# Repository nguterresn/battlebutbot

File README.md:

# BattleButBot: Your Ultimate Antweight Pusher Robot Companion

BattleButBot is a small (<10x8cm) and light (<150g) robot designed specifically for the [Antweight class of robot combat events](https://www.robotwars101.org/ants/rules.htm). With its sleek design, sturdy construction, and advanced control features, BattleButBot is the perfect choice for robot fighting enthusiasts of all skill levels.

## Features

* **Intuitive Web-based Control**: BattleButBot can be easily controlled from any device with a [web browser](#web-robot-controller), allowing you to take full control of your robot in real-time.
* **Powerful Motors**: BattleButBot's brush DC motors provide great performance and speed, allowing your robot to deliver powerful moves.
* **Durable Build**: BattleButBot is built to withstand the toughest battles in Antweight robot combat events. Its rugged construction and impact-resistant design ensure that your robot stays in one piece, no matter how intense the fight gets.
* **Easy to Use**: BattleButBot is easy to use and requires no special skills or training. With its intuitive controls and simple setup process, you can start battling right away.

🎉 **NEW**: The BattleButBot supports [ESPNow](https://www.espressif.com/en/solutions/low-power-solutions/esp-now) protocol, thus provinding another way to be externally controlled. Check the [simple esp-now controller](https://github.com/nguterresn/simple-esp-now-controller) to know more.

## Requirements

**Cheap**: Priced under $50

* ✅ Costs 50$.

**Weight**: Equal or less than 150 milligrams

* ✅ Weigths ~110g. (PLA printed)

**Acessable**: All parts are easily available (can be obtained from anywhere)

* ✅ Parts can be found on [LCSC](lcsc.com), [Digikey](digikey.com) or [AliExpress](https://www.aliexpress.us).

**Flexible**: Can be controlled over WiFi

* ✅ Easy to use web browser GUI

**Simple**: All hardware components are easy to assemble

* ✅ The device uses [PH sockets](https://www.jst-mfg.com/product/index.php?series=199) and requires a few screws.

**Portable**: Powered by a battery

* ✅ Small and light weight 2S 7.4V battery (58 x 18 x 19 mm).

## ESPNow Controller

Take a look [here](https://github.com/nguterresn/simple-esp-now-controller).

## Web Robot Controller

Connect to the `BattleButBot` network using WiFi.

Open `bot.local` on you browser.

To control the BattleButBot, simply use both **joysticks** located in the screen.

> [!NOTE]
> Before submitting a issue ticket, please use another browser as Safari is not 100% stable for a web browser controller.

### Robot Controls

You can control BattleButBot using the joysticks from the graphical user interface (GUI). To move forward, drag the left joystick upwards, and to move backward, drag the left joystick downwards. To lean the BattleButBot to the right, drag the right joystick to the right and vice-versa.

### Settings

To configure your joystick settings, click the `Settings` button.

For ease of development while the robot firmware is in development, a console log is located at the bottom of the screen.

## How to order

### Shopping list:

| Hardware                                                                                                                                                                                                                                                                                                                                                                                                                                                        | Qty | Price                           |
| --------------------------------------------------------------------------------------------------------------------------------------------------------------------------------------------------------------------------------------------------------------------------------------------------------------------------------------------------------------------------------------------------------------------------------------------------------------- | --- | ------------------------------- |
| [N20 Gear Motor 6V 600RPM](https://www.aliexpress.us/item/3256803245120861.html?spm=a2g0o.productlist.main.3.be16dmKLdmKLdh&algo_pvid=1b8b9a20-a58e-4537-a37a-af46f9d1652b&algo_exp_id=1b8b9a20-a58e-4537-a37a-af46f9d1652b-1&pdp_npi=4%40dis%21SEK%2125.63%2119.17%21%21%212.34%211.75%21%40211b61a417119945526086789eb5a6%2112000025761667070%21sea%21SE%210%21AB&curPageLogUid=N7UsGzjkJw8d&utparam-url=scene%3Asearch%7Cquery_from%3A&gatewayAdapt=glo2usa) | 2   | 1.36$ x 2 + 2.27$ shipping      |
| [Wheels](https://www.aliexpress.com/item/33026783171.html?spm=a2g0o.order_list.order_list_main.102.76381802470tYv)                                                                                                                                                                                                                                                                                                                                              | 2   | ~1$ + 4$ shipping               |
| [BOM](https://github.com/nguterresn/battlebutbot/blob/main/board/bubblebutbot/production/bom.csv)                                                                                                                                                                                                                                                                                                                                     | 1   | ~10$ + 10$ [shipping](LCSC.com) |
| [PCB](https://github.com/nguterresn/battlebutbot/blob/main/board/bubblebutbot/production/bubblebutbot.zip)                                                                                                                                                                                                                                                                                                                                  | 5   | ~2$ + 3$ [shipping](jlcpcb.com) |
| [2S LiPo](https://botland.store/battery-li-pol-2s-74-v/570-li-poly-dualsky-520mah-25c-2s-74v-6941047107427.html)                                                                                                                                                                                                                                                                                                                                                | 1   | 8$                              |
| Total                                                                                                                                                                                                                                                                                                                                                                                                                                                           | -   | ~50$                            |

When ordering the BOM, make sure to order at least 5 (five!) of each component so you end up with the possibility to solder 5 different PCBs.

### Supply chain troubleshooting

⚠️ In case a few componenets are not available refer to the list below:

- Any ESP32-S3-WROOM-1 (NOT 1U!) should work. There are a [few variations](https://www.lcsc.com/search?q=ESP32-S3-WROOM-1) of the same footprint with more or less RAM and FLASH.
- H1-H4 componenets are mount holes, they don't need any component assigned.
- In case of resistor or capacitors shortage, it is also OK to find other supplier as long as it follows the same specification (e.g. 20k resistor 5%)

## Design

The design of the BattleButBot plays an important role. How it is designed determines how heavy (or how light) it is. Two requirements: sturdy and light.

### Cyberpunk

A cyberpunk alike robot is cold as hell. The low poly edges also make it easier to print.

## Assemble

What you need:

* 6 M3 8mm/5mm screws
* 6 Heat inserts
* The [body](https://github.com/nguterresn/battlebutbot/blob/main/body/Car.stl)
* The [lid](https://github.com/nguterresn/battlebutbot/blob/main/body/Lid.stl)
* The [front](https://github.com/nguterresn/battlebutbot/blob/main/body/Gate.stl)
* A 2S-7.4V Battery
* The [PCB](https://github.com/nguterresn/battlebutbot/tree/main/board/bubblebutbot)
* The two wheels

### Battery

Place the battery close to the front of the bot.

Place the switch.

### Motors

Place both motors with the gears facing the top (to prevent any friction with the bottom).

### PCB

Before screwing the PCB down, finish all the connections.

Place the PCB and the lid, and screw it down.

## Develop

Clone the project by running the following command:

```bash
git clone git@github.com:nguterresn/battlebutbot.git
```

### Tools

* VSCode with PlatformIO
* Fusion360

### 3rd Party Libraries

* [ESPAsyncWebServer](https://github.com/me-no-dev/ESPAsyncWebServer)
* [Joystick 2](https://github.com/bobboteck/JoyStick)

## Support

If you have any questions or issues with the BattleButBot, please contact guterresnogueira@gmail.com.

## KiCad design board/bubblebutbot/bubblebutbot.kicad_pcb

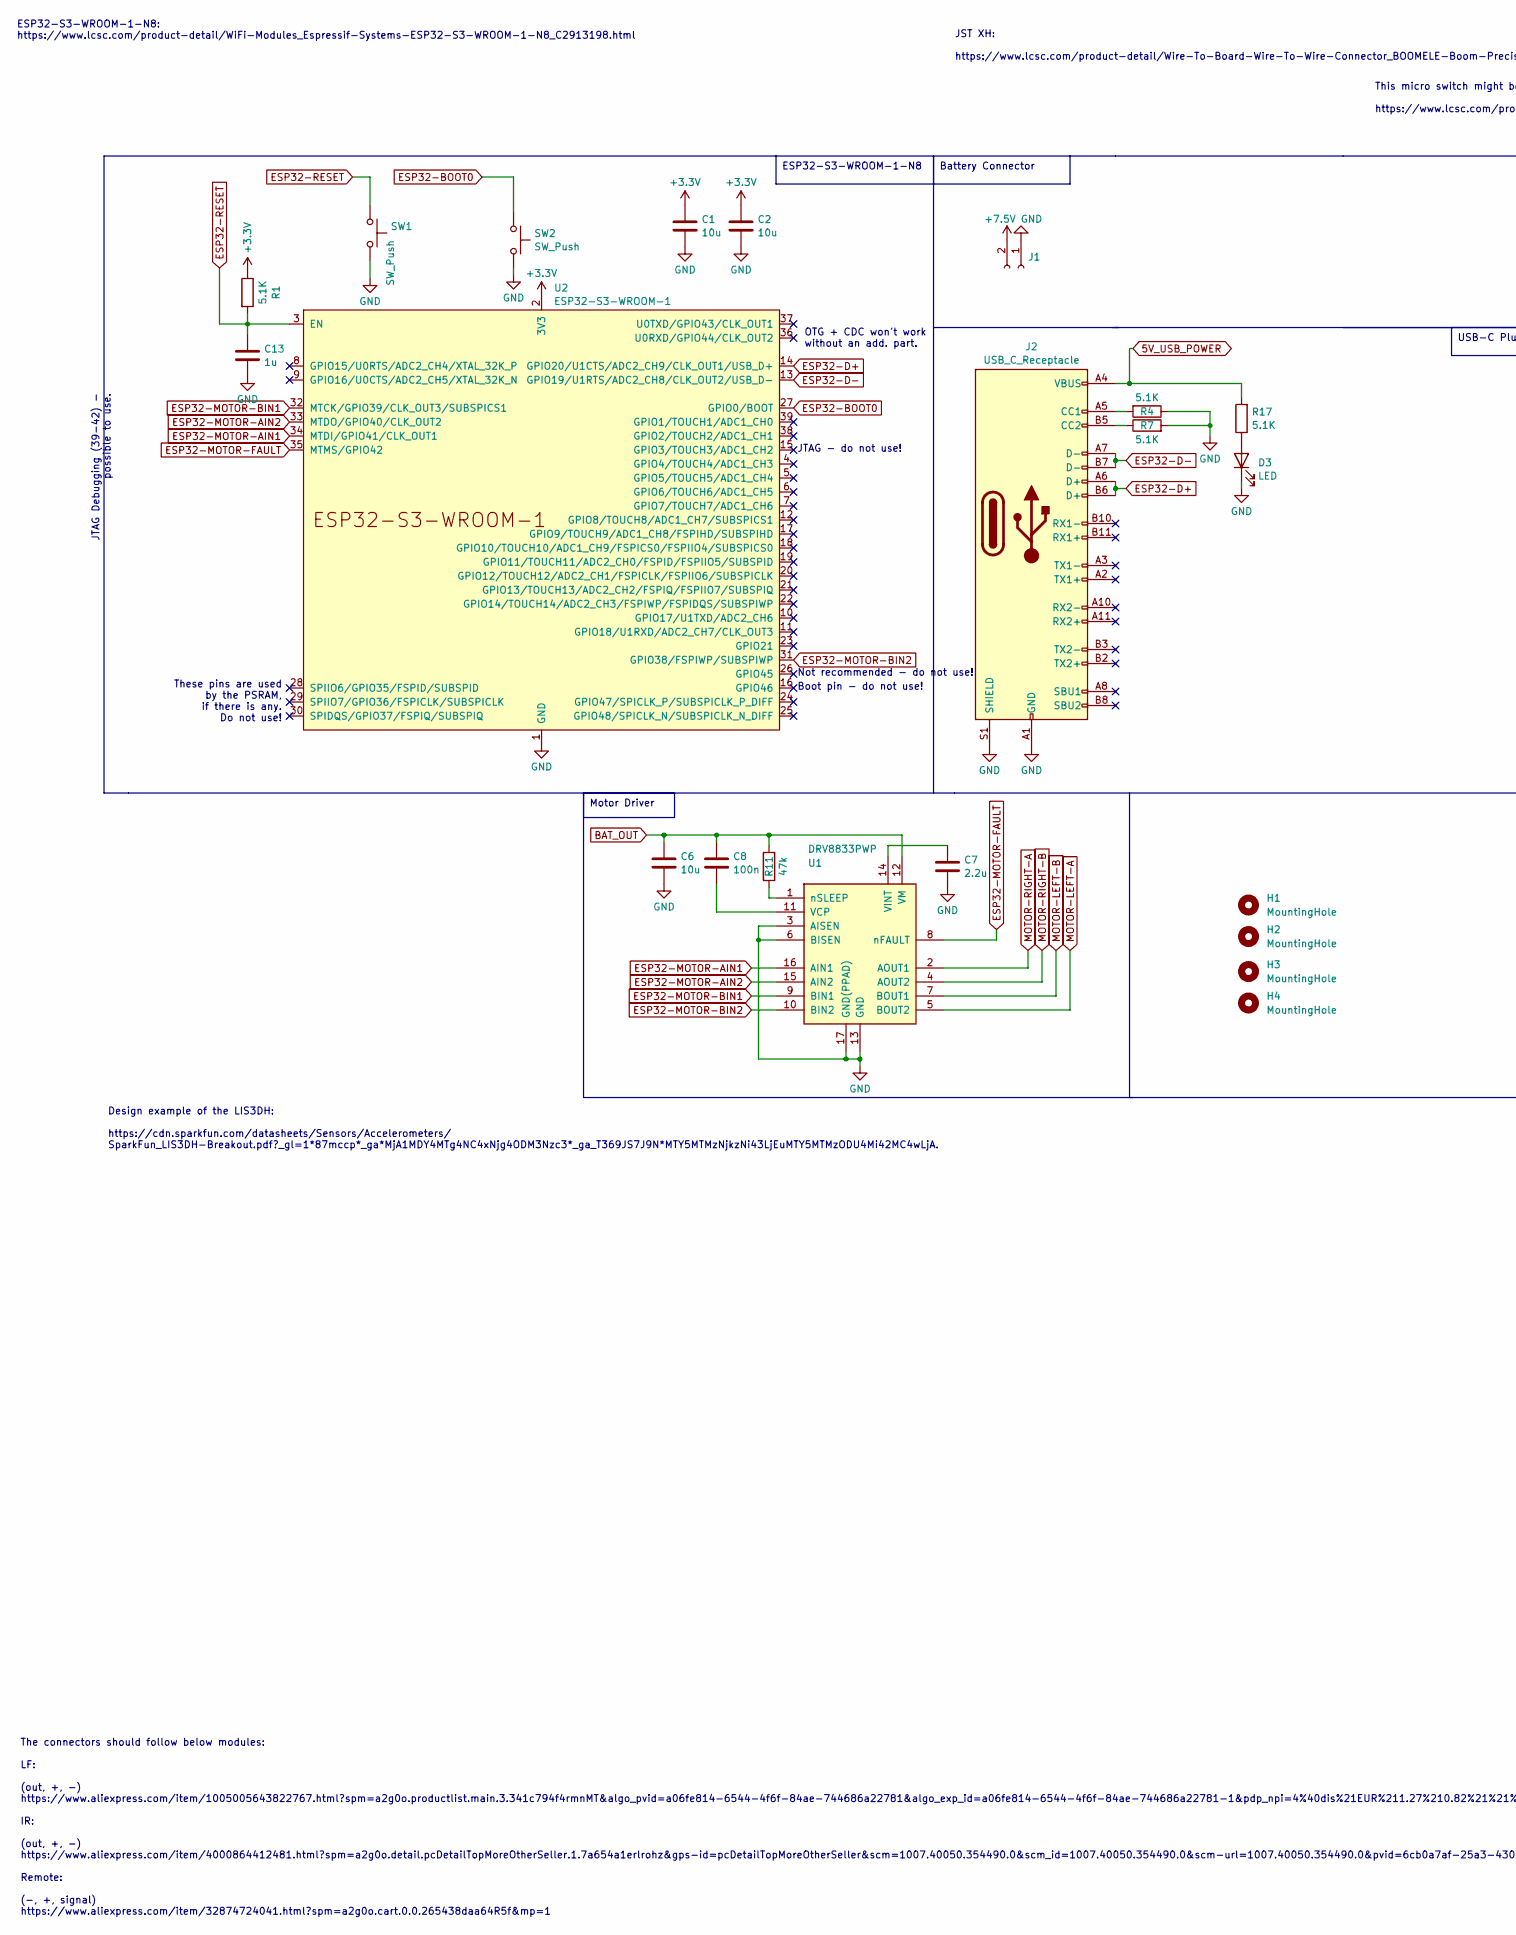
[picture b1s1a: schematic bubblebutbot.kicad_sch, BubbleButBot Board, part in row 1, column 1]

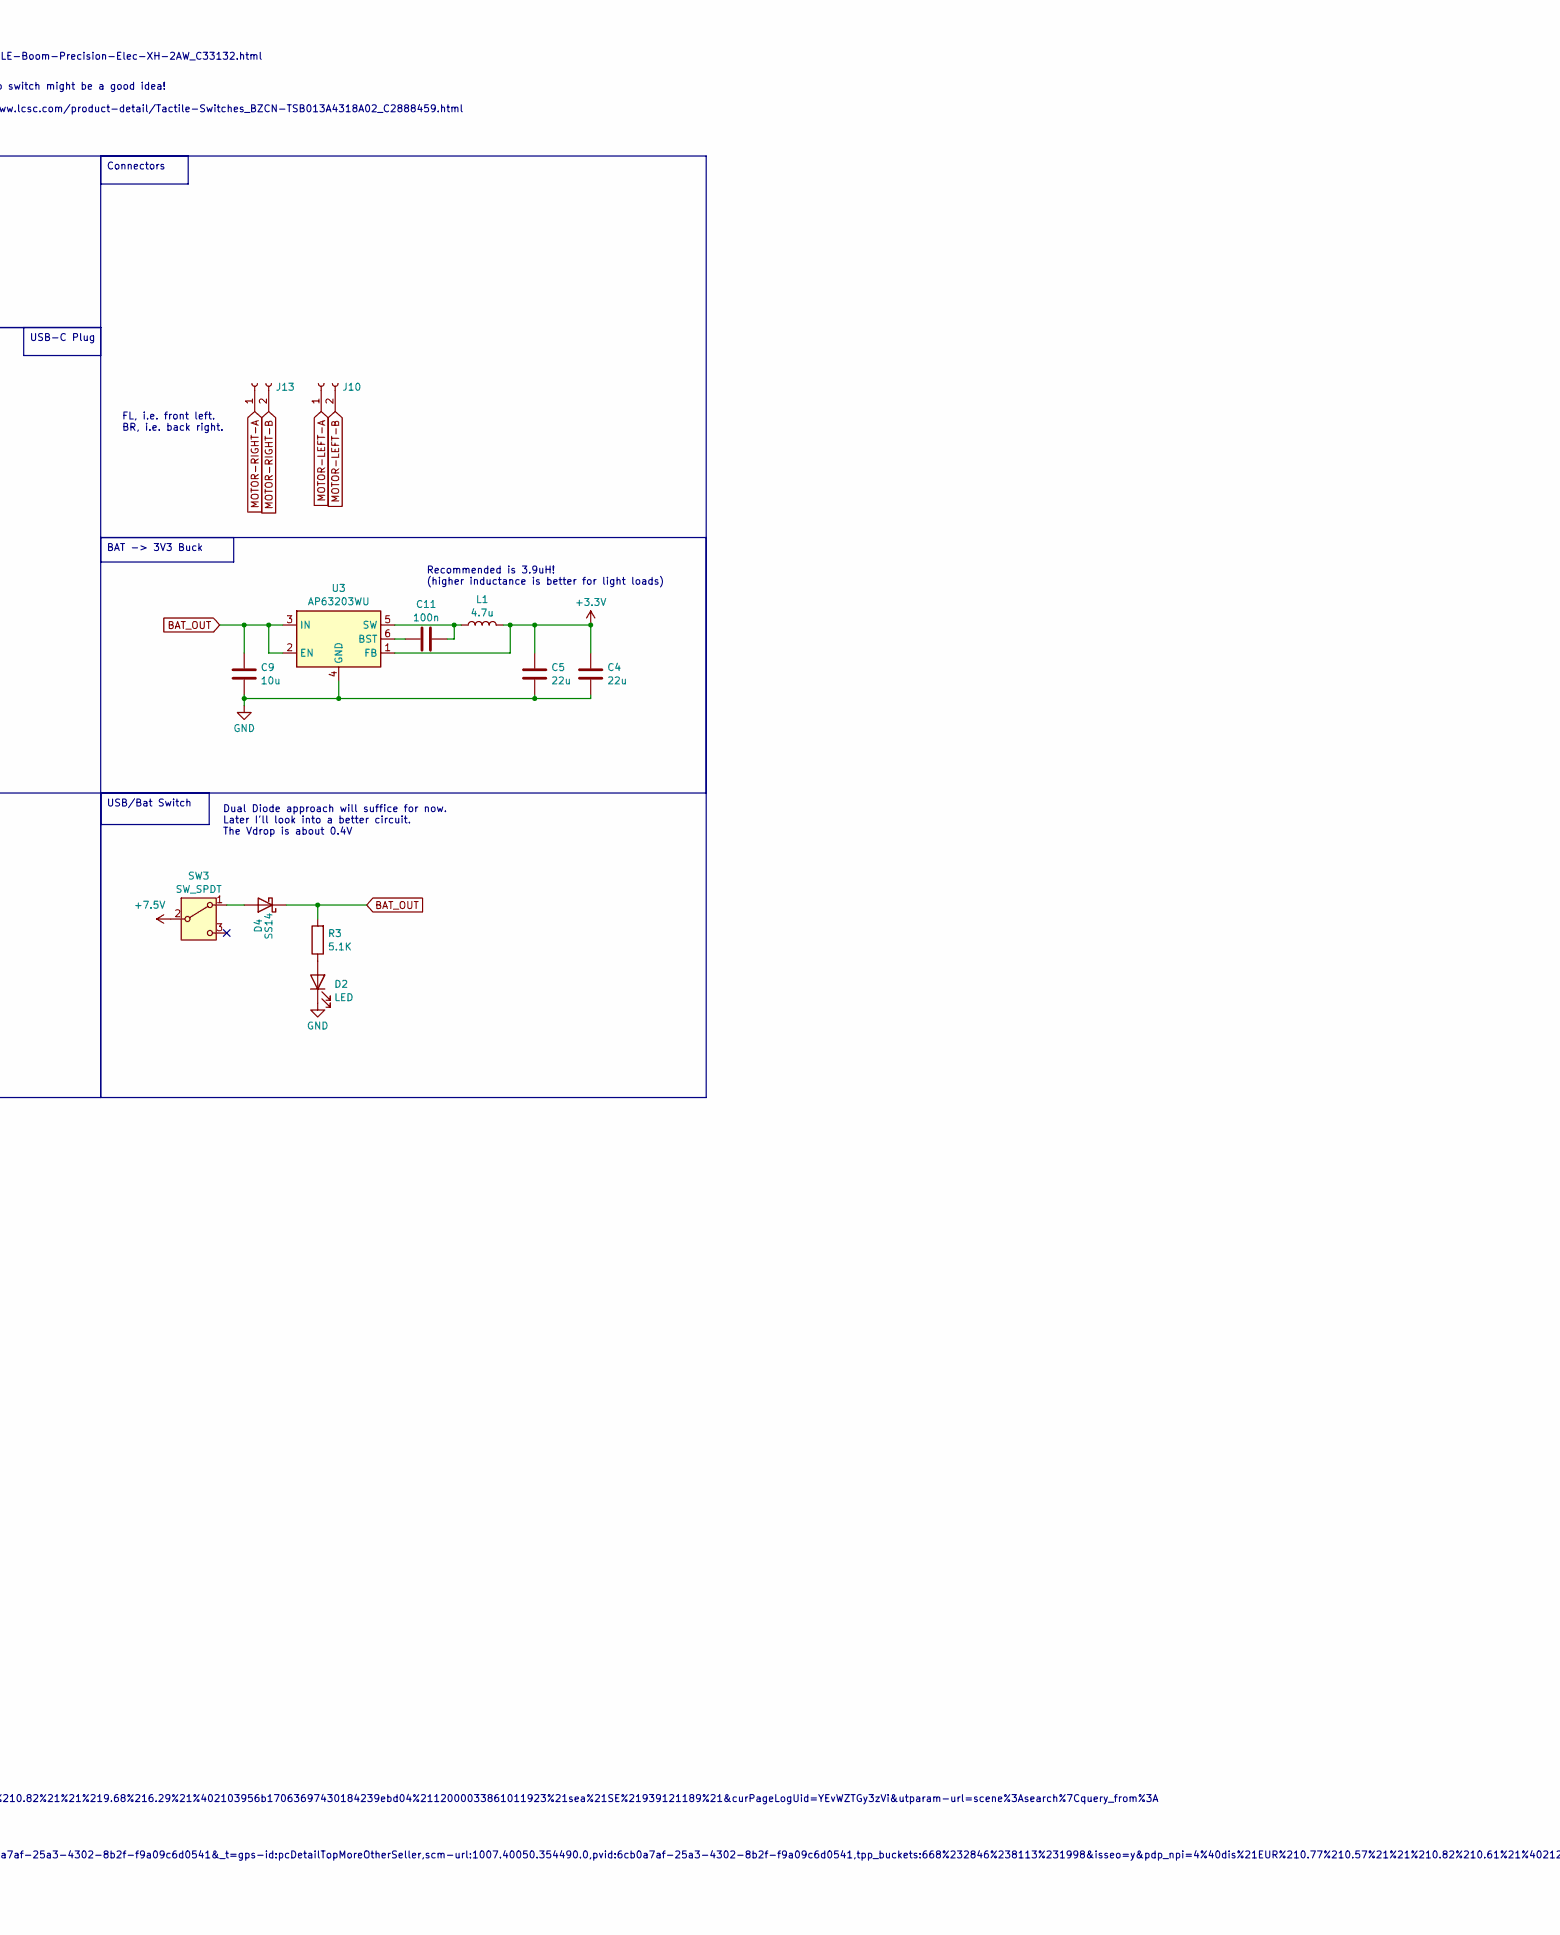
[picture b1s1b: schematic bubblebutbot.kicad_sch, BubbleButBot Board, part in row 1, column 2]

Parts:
C1, C2, C9: 10u; C_0603_1608Metric_Pad1.08x0.95mm_HandSolder; LCSC C380316
C4, C5: 22u; C_1206_3216Metric_Pad1.33x1.80mm_HandSolder; LCSC C12891
C6: 10u; C_1206_3216Metric_Pad1.33x1.80mm_HandSolder; LCSC C47971
C7: 2.2u; C_0603_1608Metric_Pad1.08x0.95mm_HandSolder; LCSC C2691406
C8, C11: 100n; C_0603_1608Metric_Pad1.08x0.95mm_HandSolder; LCSC C282519
C13: 1u; C_0603_1608Metric_Pad1.08x0.95mm_HandSolder; LCSC C1592
D2, D3: LED; LED_0603_1608Metric_Pad1.05x0.95mm_HandSolder; LCSC C965799
D4: SS14; D_SMA; LCSC C2480
H1, H2, H3, H4: MountingHole; MountingHole_3.2mm_M3_ISO14580_Pad
J1, J10, J13: JST XH; JST_PH_S2B-PH-K_1x02_P2.00mm_Horizontal; LCSC C722769
J2: USB_C_Receptacle; USB_C_Receptacle_GCT_USB4105-xx-A_16P_TopMnt_Horizontal; LCSC C2765186
L1: 4.7u; L_Wuerth_WE-TPC-3816; LCSC C2879693
R1, R3, R4, R7, R17: 5.1K; R_0603_1608Metric_Pad0.98x0.95mm_HandSolder; LCSC C2907114
R11: 47k; R_0603_1608Metric_Pad0.98x0.95mm_HandSolder; LCSC C2907173
SW1, SW2: SW_Push; SW_SPST_CK_RS282G05A3; LCSC C2888455
SW3: SW_SPDT; SW_Slide_SPDT_Straight_CK_OS102011MS2Q; LCSC C2939725
U1: DRV8833PWP; HTSSOP-16-1EP_4.4x5mm_P0.65mm_EP3.4x5mm_Mask2.46x2.31mm_The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; LCSC C50506
U2: ESP32-S3-WROOM-1; LCSC C2913198
U3: AP63203WU; TSOT-23-6; LCSC C780769

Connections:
5V_USB_POWER: J2.A4 (VBUS), J2.A9 (VBUS), J2.B4 (VBUS), J2.B9 (VBUS), R17.2
+3.3V: C1.1, C2.1, C4.1, C5.1, L1.2, R1.1, U2.2 (3V3), U3.1 (FB)
+7.5V: J1.2, SW3.2 (B)
BAT_OUT: C6.1, C8.2, C9.1, D4.1 (K), R3.2, R11.2, U1.12 (VM), U3.2 (EN), U3.3 (IN)
ESP32-BOOT0: SW2.1, U2.27 (GPIO0/BOOT)
ESP32-D+: J2.A6 (D+), J2.B6 (D+), U2.14 (GPIO20/U1CTS/ADC2_CH9/CLK_OUT1/USB_D+)
ESP32-D-: J2.A7 (D-), J2.B7 (D-), U2.13 (GPIO19/U1RTS/ADC2_CH8/CLK_OUT2/USB_D-)
ESP32-MOTOR-AIN1: U1.16 (AIN1), U2.34 (MTDI/GPIO41/CLK_OUT1)
ESP32-MOTOR-AIN2: U1.15 (AIN2), U2.33 (MTDO/GPIO40/CLK_OUT2)
ESP32-MOTOR-BIN1: U1.9 (BIN1), U2.32 (MTCK/GPIO39/CLK_OUT3/SUBSPICS1)
ESP32-MOTOR-BIN2: U1.10 (BIN2), U2.31 (GPIO38/FSPIWP/SUBSPIWP)
ESP32-MOTOR-FAULT: U1.8 (nFAULT), U2.35 (MTMS/GPIO42)
ESP32-RESET: C13.1, R1.2, SW1.1, U2.3 (EN)
GND: C1.2, C2.2, C4.2, C5.2, C6.2, C7.2, C9.2, C13.2, D2.1 (K), D3.1 (K), J1.1, J2.A1 (GND), J2.A12 (GND), J2.B1 (GND), J2.B12 (GND), J2.S1 (SHIELD), R4.1, R7.2, SW1.2, SW2.2, U1.3 (AISEN), U1.6 (BISEN), U1.13 (GND), U1.17 (GND(PPAD)), U2.1 (GND), U2.40 (GND), U2.41 (GND), U3.4 (GND)
MOTOR-LEFT-A: J10.1, U1.5 (BOUT2)
MOTOR-LEFT-B: J10.2, U1.7 (BOUT1)
MOTOR-RIGHT-A: J13.1, U1.2 (AOUT1)
MOTOR-RIGHT-B: J13.2, U1.4 (AOUT2)
unnamed: D2.2 (A), R3.1
unnamed: D3.2 (A), R17.1
unnamed: D4.2 (A), SW3.1 (A)
unnamed: J2.A5 (CC1), R4.2
unnamed: J2.B5 (CC2), R7.1
unnamed: C8.1, U1.11 (VCP)
unnamed: C7.1, U1.14 (VINT)
unnamed: R11.1, U1.1 (nSLEEP)
unnamed: C11.2, U3.6 (BST)
unnamed: C11.1, L1.1, U3.5 (SW)

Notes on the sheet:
Battery Connector
USB-C Plug
BAT -> 3V3 Buck
USB/Bat Switch
Connectors
Motor Driver
ESP32-S3-WROOM-1-N8
ESP32-S3-WROOM-1-N8: https://www.lcsc.com/product-detail/WiFi-Modules_Espressif-Systems-ESP32-S3-WROOM-1-N8_C2913198.html
This micro switch might be a good idea! https://www.lcsc.com/product-detail/Tactile-Switches_BZCN-TSB013A4318A02_C2888459.html
Design example of the LIS3DH: https://cdn.sparkfun.com/datasheets/Sensors/Accelerometers/ SparkFun_LIS3DH-Breakout.pdf?_gl=1*87mccp*_ga*MjA1MDY4MTg4NC4xNjg4ODM3Nzc3*_ga_T369JS7J9N*MTY5MTMzNjkzNi43LjEuMTY5MTMzODU4Mi42MC4wLjA.
JTAG Debugging (39-42) - possible to use.
JST XH: https://www.lcsc.com/product-detail/Wire-To-Board-Wire-To-Wire-Connector_BOOMELE-Boom-Precision-Elec-XH-2AW_C33132.html
JTAG - do not use!
Dual Diode approach will suffice for now. Later I'll look into a better circuit. The Vdrop is about 0.4V
OTG + CDC won't work without an add. part.
The connectors should follow below modules: LF: (out, +, -) https://www.aliexpress.com/item/1005005643822767.html?spm=a2g0o.productlist.main.3.341c794f4rmnMT&algo_pvid=a06fe814-6544-4f6f-84ae-744686a22781&algo_exp_id=a06fe814-6544-4f6f-84ae-744686a22781-1&pdp_npi=4%40dis%21EUR%211.27%210.82%21%21%2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
Boot pin - do not use!
FL, i.e. front left. BR, i.e. back right.
These pins are used by the PSRAM, if there is any. Do not use!
Recommended is 3.9uH! (higher inductance is better for light loads)
Not recommended - do not use!

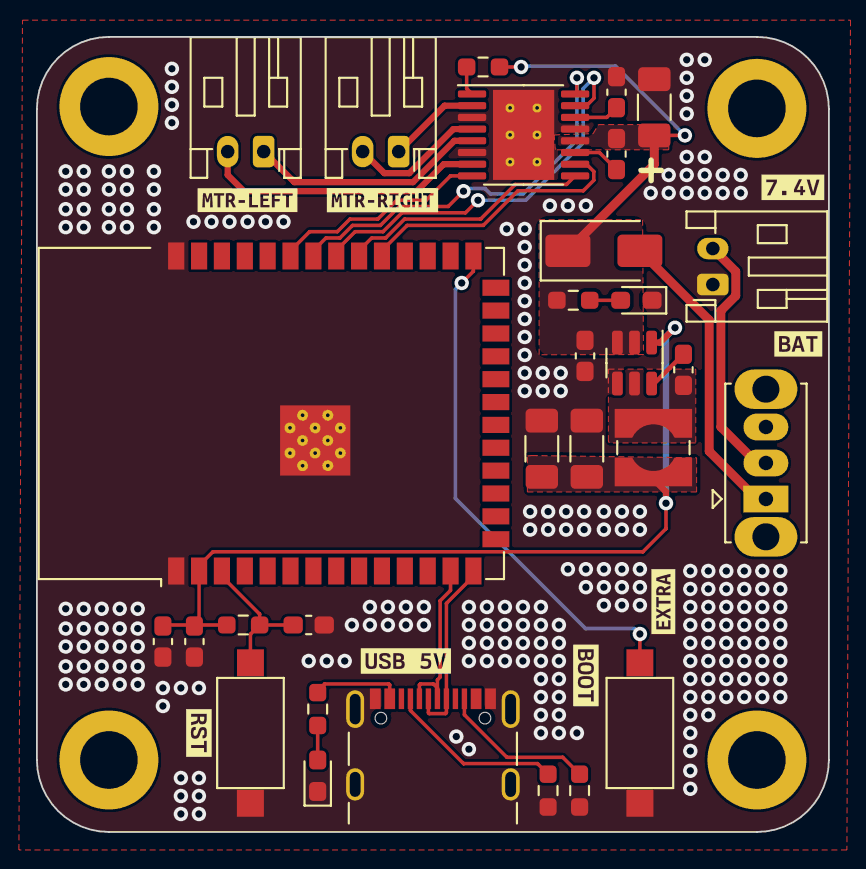
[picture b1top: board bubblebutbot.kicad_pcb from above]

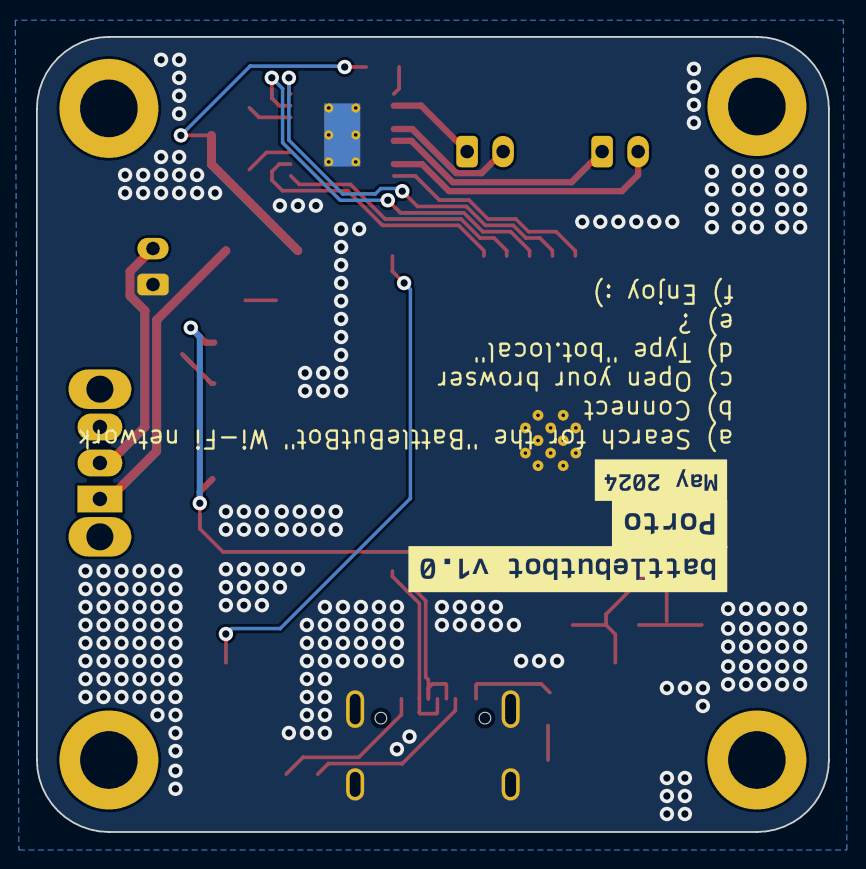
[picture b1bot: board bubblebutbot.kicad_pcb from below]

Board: 2 copper layers, 44.0 x 44.2 mm, 45 parts (3 on the bottom side), 28 nets.

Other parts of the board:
kibuzzard-65B53DEB: G***; kibuzzard-65B53DEB
kibuzzard-65B534AD: G***; kibuzzard-65B534AD
kibuzzard-65B534B8: G***; kibuzzard-65B534B8
kibuzzard-65B5357F: G***; kibuzzard-65B5357F
kibuzzard-65B52192: G***; kibuzzard-65B52192
kibuzzard-65B53096: G***; kibuzzard-65B53096
kibuzzard-65B53575: G***; kibuzzard-65B53575
kibuzzard-661BA04B: G***; kibuzzard-661BA04B
kibuzzard-664E35A6: G***; kibuzzard-664E35A6
kibuzzard-664E35B1: G***; kibuzzard-664E35B1
kibuzzard-664E35C5: G***; kibuzzard-664E35C5

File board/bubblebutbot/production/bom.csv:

Designator,Footprint,Quantity,Value,LCSC Part #
"C1, C2, C9",0603,3,10u,C380316
"C11, C8",0603,2,100n,C282519
C13,0603,1,1u,C1592
"C4, C5",1206,2,22u,C12891
C6,1206,1,10u,C47971
C7,0603,1,2.2u,C2691406
"D2, D3",0603,2,LED,C965799
D4,D_SMA,1,SS14,C2480
"H1, H2, H3, H4",MountingHole_3.2mm_M3_ISO14580_Pad,4,MountingHole,
"J1, J10, J13",JST_PH_S2B-PH-K_1x02_P2.00mm_Horizontal,3,JST XH,C722769
J2,USB_C_Receptacle_GCT_USB4105-xx-A_16P_TopMnt_Horizontal,1,USB_C_Receptacle,C2765186
L1,L_Wuerth_WE-TPC-3816,1,4.7u,C2879693
"R1, R17, R3, R4, R7",0603,5,5.1K,C2907114
R11,0603,1,47k,C2907173
"SW1, SW2",SW_SPST_CK_RS282G05A3,2,SW_Push,C2888455
SW3,SW_Slide_SPDT_Straight_CK_OS102011MS2Q,1,SW_SPDT,C2939725
U1,HTSSOP-16-1EP_4.4x5mm_P0.65mm_EP3.4x5mm_Mask2.46x2.31mm_ThermalVias,1,DRV8833PWP,C50506
U2,ESP32-S3-WROOM-1,1,ESP32-S3-WROOM-1,C2913198
U3,TSOT-23-6,1,AP63203WU,C780769

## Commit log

2022-11-06 A bunch of new files
2022-11-08 Scan BT is working + web (bt connect is still to be implemented)
2022-12-01 Removed BLE support. Joystick using Wifi
2022-12-01 Changes on GUI
2022-12-01 changed gitignore
2022-12-03 Adapted code to support more boards
2022-12-03 Fixed dns for esp8266
2022-12-03 Driver is ready. needs some tweaking.
2022-12-04 Support for two motors
2022-12-04 Removed action button for now. Motor update still up to improvements.
2022-12-04 A few more changes but yet done.
2022-12-07 A very hacky way of controlling the motors.
2022-12-07 removed logs
2022-12-15 improved motor motion
2022-12-17 Some minor cleaning and added a todo
2022-12-18 Added Doxygen comments to the MachineRoom class, added brake method and simplified /fixed once and for all the motor controller code.
2022-12-19 Added speed o meter :D
2022-12-20 redesigned web server home page
2022-12-21 some changes on the web server html page and heap memory debug.
2022-12-21 Limited the number of Wifi connections.
2022-12-21 reduced LOC out of html home page
2022-12-21 increased lwIP bandwidtrh and flash freq
2022-12-21 Fixed blank page on consecutive refreshes
2022-12-21 Fixed some other heap memory issue.
2022-12-24 reduced html LOC
2022-12-24 no longer stops the joystick due to a second touch
2022-12-25 Added action button to the html front page.
    i am going to keep the design like this until I have more resources to put into design/css/html etc. From now on, focusing on hw and 3d design to make this happen.
2022-12-25 Missing id on action button!
2023-01-02 Added the prototype 3d model files
2023-01-03 Added 3rd party libraries and Tools sections.
2023-01-03 Lighter car body for the protoype
2023-01-29 added belt and nav v1
2023-02-01 added testrig
2023-02-03 Added pinout diagram
2023-03-12 dev board schematic done. Started design
2023-03-18 new design for the prototype
2023-03-19 updated designs
2023-03-19 added uncrustify formatter
2023-03-19 Added a connect feedback using the motors.
2023-03-19 Reverted the analog pwm value from 100 to 255.
2023-03-21 Rotation based on the module. X and Y limited to the circunference of the joystick circle.
2023-03-24 Update designs. Minor changes
2023-03-24 Added connection feedback.
2023-03-24 A small change.
2023-03-25 Finished prototype pcb
2023-03-25 ignore kicad cache
2023-03-25 added bigger wheels
2023-03-25 Moved BOM files into a new folder.
2023-03-25 changing the name of the robot to `battlebutbot``
2023-03-26 Fetch the `.html` web page from the SPIFFS file system instead of storing it in the sketch flash
2023-03-26 Added config page. proper design, logic and memory management missing.
2023-04-02 redesigned the home page with flexbox and a minimal css framework, a mix between the skeleton and a grid system. Css file is not external
2023-04-02 save configuration on the EEPROM. A few changes on the config web page.
2023-04-02 prevent scrol on the web page.
2023-04-19 Added a missing inductor to the design
2023-05-09 gerber for 1v01 ready
2023-05-17 pcb step file, new attempt to have a functioning prototype with a battery holder and some code formatting.
2023-05-19 Naming.
2023-05-19 Introduced friction step. Still a lot of work to be done.
2023-05-21 speed and friction fields ready to be updated by the web client.
2023-05-21 Changed config.html to include the speed and the friction as a range slider.
2023-05-21 Added speed and friction to the EEPROM
2023-05-25 New wheels with steps
2023-05-26 loading the configuration is possible now. Changing the switches and sliders is the only step left to do.
2023-05-30 Added a way to format the configuration into hex format to keep the same size even with diffferent values.
2023-06-02 Update values from the configuration stored on eeprom on the web config page
2023-06-02 Commented out the friction code. Doesnt work properly. Added backwards directions.
2023-06-04 Added servo init code.
2023-06-04 Include flip mechanism for the servo
2023-06-06 New ServoMotor class
2023-06-06 Added battery level to config html page.
2023-06-10 Prevent double tap zoom in the web page. Allow multi-touch actions
2023-06-10 shadow boxes
2023-06-11 Added doxygen docs and few new comments to the code.
2023-06-11 no need to pass so many pins around
2023-06-11 Added method to brake inside Motor class
2023-06-18 remove doxygen files
2023-06-18 Added new todos
2023-06-19 Changed Motor control to be with slow decay instead of fast decay
2023-06-19 Moved some files into folders
2023-06-19 added transmitter folder
    roundrobin of 1-2 ms using espnow library
2023-06-20 Moved the cnfiguration change to the Machine Room and added a enabled field for the servo
2023-06-20 Added a test to the ServoMotor class.
2023-06-20 transmitt MPU6050 data
2023-06-21 added espnow to main firmware as receiver
    WIP, memcpy causing OOM
2023-06-22 test
2023-06-25 Added support for ESP32 and a custom partition for it to use more app memory and less spiffs/ota second bankl
2023-06-25 esp32 working on esp-idf and arduino at the same time.
2023-06-27 Added arduino compoenent.
2023-06-28 Added arduino libraries as a components. Rewrote the servo class to use hal libraries.
2023-06-28 components
2023-06-29 Some clean up
2023-07-01 Added auto mode
2023-07-04 moved req.md
2023-07-15 Added buzzer
2023-07-15 A few improvements.
2023-07-15 small improv.
2023-07-23 first steps into the final prod pcb!
2023-07-23 added acc and 3v3 buck
2023-07-24 Added some more pins and set up the DIPx4
2023-08-06 A few additions: new acc and motor driver schematics.
2023-08-09 added buck to 5V
2023-08-13 finished schematic and BOM. Design is ready to start!
2023-08-28 a few more improvements here and there. Almost there.
2023-09-17 pcb done!
2023-10-01 generated new ibom.html
2023-10-01 deleted cached files
2023-10-01 git checkout 2.0.13
2023-10-01 Create sdkconfig.esp32-s3-devkitc-1
2023-10-01 Had to change the platform esp-idf to 5.4.0
2023-10-07 support for esp32s3
2023-10-08 first prod body version
2023-10-14 Moved a couple of files over to include/src folders. Removed ledc lib call and addded ESP32Servo lib
2023-10-14 Removed Robot class
2023-10-14 Added robot_flip
2023-10-14 Removed the MachineRoom class and replaced with normal code
2023-10-14 A few more changes...
2023-10-14 A few fixes for freeRTOS tasks.
2023-11-04 a few comments
2023-11-05 brake on start
2023-11-08 working for esp wroom 32
2023-11-08 working test code for espnow with esp wroom 32
2023-11-09 create bot folder
2023-11-09 more bot, not working
2023-11-12 Removed Buzzer. Added support for ESP32 ("S1")
2023-11-12 pcb 1v04
2023-11-12 small fix
2023-11-20 new testing prod designs
2023-11-22 Added as drift slider
2023-11-22 drift from float to int
2023-11-22 Redundant way of storing the drift value
2023-11-22 compilable !
2023-11-22 fixed drift
2023-11-22 Revert "Added as drift slider"
    This reverts commit 1904178970575699550478b9d1a593eb7e742978.
2023-11-25 simplified the handle of the configuration
2023-11-25 Preparing for trouble 😈
2023-11-25 Drift Ratio to Motor!
2023-11-25 Solidify the drift ratio logic
2023-11-26 drift added
2023-11-26 Fixed EEPROM
2023-11-26 A few last changes.
2023-11-26 Fixed small bug on config.html
2023-11-28 added espnow, wip
2023-11-28 very bad menu
2023-11-28 oled driver, tasks for oled and espnow
2023-11-28 add transmitter firmware wip
2023-11-30 buttons and joysticks working
2023-12-02 pcb v0.5
    smaller
2023-12-02 new prod deisgn
2023-12-04 started working on transmitter pcb
2023-12-04 realise the oled I have is 128x64 lol
2023-12-07 fix oled for 128x64 size
2024-01-04 gerber prod 1v05
2024-01-12 Added acceleratiom
2024-01-14 Fixed speed config step
2024-01-14 Comments
2024-01-14 Drift is still not working. A few other fixes and comments!
2024-01-15 Separated the periodic from the espontaneous events
2024-01-15 Some other fixes
2024-01-16 theres a bug when the car drives backwards
2024-01-17 replaced arduino analogWrite by ledC arduino wrapper
2024-01-20 A few improvements
2024-01-24 v2.06 schamtic
2024-01-25 Working on the new version ... 🚀
2024-01-27 VERSION 1.06
2024-01-28 added new v06 step
2024-02-03 prod 1v7
2024-02-04 added 2 joytsticks
2024-02-04 removed unused code
2024-03-01 Better UI
2024-06-02 readme updated
2024-07-27 added support for a esp now controller
2024-11-23 firmware updated to support browser and physical controller depending on a macro
2024-11-23 a few changes on the overall structure
2024-11-23 removed a few files from the repo
2024-11-23 Revert "Delete board/bubblebutbot/CustomFootprints.pretty directory"
    This reverts commit 6db3985a11108fd87f6f82ed4c36b4b392f95506.
2024-11-23 the correct gitignore
2024-11-23 another attempt
2024-11-23 missing one file.
2024-11-23 One less folder
2024-11-23 pcb v1.0 - gate 1.0
2024-11-23 updated.
2024-11-23 updated designs to match the PCB v1.0
2024-11-24 added a note
2024-11-24 fixed a few things and added awesome gifs!
2025-01-01 fixed http request concurrency
2025-01-01 board 1.1 something
2025-01-02 bug fixes
2025-01-05 updated front screws
2025-05-10 removed uart printfs
2025-05-10 improved design
